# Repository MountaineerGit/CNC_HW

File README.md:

STM32 breakoutboard for custom CNC machine

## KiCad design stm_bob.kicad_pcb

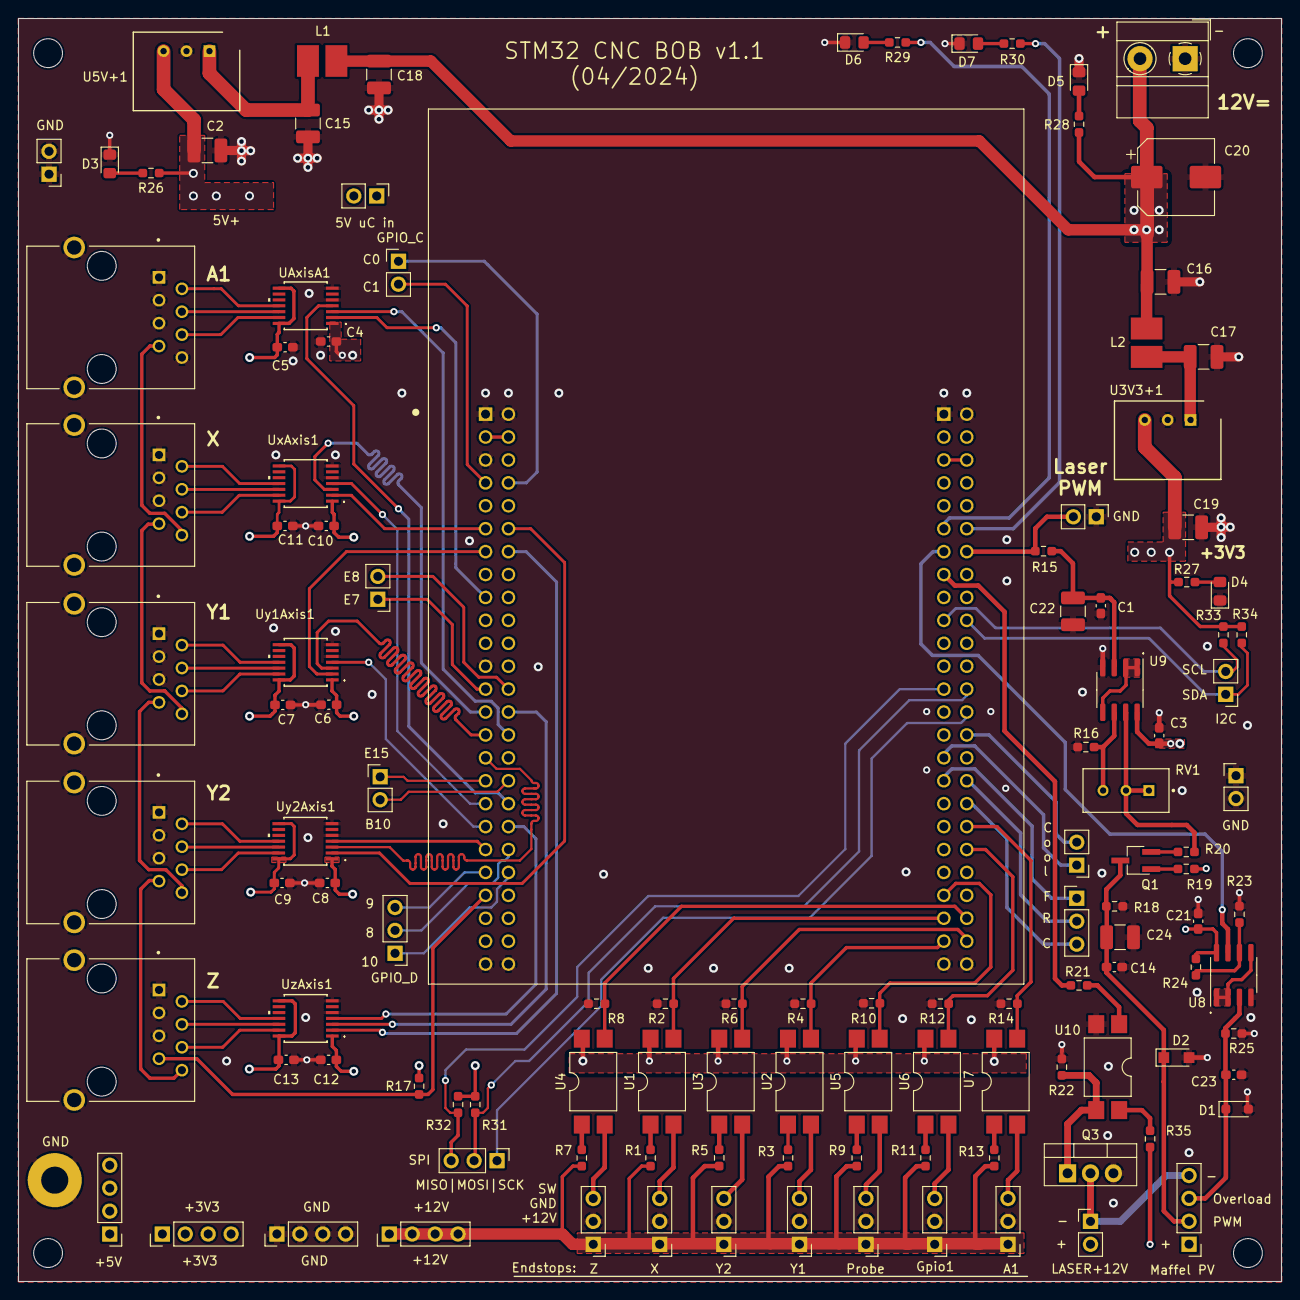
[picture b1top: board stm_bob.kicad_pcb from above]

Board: 4 copper layers, 140.0 x 140.0 mm, 125 parts (0 on the bottom side), 107 nets.

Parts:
C1, C21: 100n; C_0603_1608Metric_Pad1.08x0.95mm_HandSolder
C2, C15, C16, C17, C18, C19: 10uF 100V MCC; L_1210_3225Metric_Pad1.42x2.65mm_HandSolder
C3, C4, C5, C6, C7, C8, C9, C10, C11, C12, C13, C14: C; C_0603_1608Metric_Pad1.08x0.95mm_HandSolder
C20: C_Polarized; CP_Elec_8x10
C22, C24: 10uF; L_1210_3225Metric_Pad1.42x2.65mm_HandSolder
C23: 10pf; C_0603_1608Metric_Pad1.08x0.95mm_HandSolder
D1: 10V; D_SOD-323_HandSoldering
D2: D_Zener; Nexperia_CFP3_SOD-123W
D3, D4, D5, D6, D7: LED; D_0805_2012Metric_Pad1.15x1.40mm_HandSolder
H1, H2, H3, H4: MountingHole; MountingHole_3.2mm_M3
H5: MountingHole_Pad; MountingHole_3mm_Pad
J1: Conn_01x02; TerminalBlock_MetzConnect_Type011_RT05502HBWC_1x02_P5.00mm_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
J2, J3, J5, J6: Conn_01x04_Pin; PinHeader_1x04_P2.54mm_Vertical
J4, J7: Conn_01x02_Pin; PinHeader_1x02_P2.54mm_Vertical
J9_GPIO1, J9_GPIO2, J9_GPIO3, J9_GPIO4, J10_GPIO1: Conn_01x02; PinHeader_1x02_P2.54mm_Vertical
J11_GPIO1, J11_SPI1, J11_SPI2: Conn_01x03; PinHeader_1x03_P2.54mm_Vertical
JAxisA1: A-2004-2-4-LPS-N-R; ASSMANN_A-2004-2-4-LPS-N-R
JGpio1: Conn_01x03_Pin; PinHeader_1x03_P2.54mm_Vertical
JI2C1: Conn_01x02; PinHeader_1x02_P2.54mm_Vertical
JLaser12V1: Conn_01x02_Pin; PinHeader_1x02_P2.54mm_Vertical
JLaserPWM1: Conn_01x02_Pin; PinHeader_1x02_P2.54mm_Vertical
JProbe1: Conn_01x03_Pin; PinHeader_1x03_P2.54mm_Vertical
JPvMaffel1: Conn_01x04_Pin; PinHeader_1x04_P2.54mm_Vertical
JlimA1: Conn_01x03_Pin; PinHeader_1x03_P2.54mm_Vertical
JlimX1: Conn_01x03_Pin; PinHeader_1x03_P2.54mm_Vertical
JlimY1, JlimY2: Conn_01x03_Pin; PinHeader_1x03_P2.54mm_Vertical
JlimZ1: Conn_01x03_Pin; PinHeader_1x03_P2.54mm_Vertical
JxAxis1: A-2004-2-4-LPS-N-R; ASSMANN_A-2004-2-4-LPS-N-R
Jy1Axis1, Jy2Axis1: A-2004-2-4-LPS-N-R; ASSMANN_A-2004-2-4-LPS-N-R
JzAxis1: A-2004-2-4-LPS-N-R; ASSMANN_A-2004-2-4-LPS-N-R
L1, L2: L; IND_S-126-R_RCP
Q1: NPN; TSOT-23_HandSoldering
Q3: IRF3205; TO-220-3_Vertical
R1, R3, R5, R7, R9, R11, R13, R15, R28, R35: 1k; R_0603_1608Metric_Pad0.98x0.95mm_HandSolder
R2, R4, R6, R8, R10, R12, R14, R17, R23, R31, R32, R33, R34: 3k3; R_0603_1608Metric_Pad0.98x0.95mm_HandSolder
R16: 47k; R_0603_1608Metric_Pad0.98x0.95mm_HandSolder
R18, R19, R20: R; R_0603_1608Metric_Pad0.98x0.95mm_HandSolder
R21, R27: 430; R_0603_1608Metric_Pad0.98x0.95mm_HandSolder
R22: 2k; R_0603_1608Metric_Pad0.98x0.95mm_HandSolder
R24: 2k2; R_0603_1608Metric_Pad0.98x0.95mm_HandSolder
R25: 100k; R_0603_1608Metric_Pad0.98x0.95mm_HandSolder
R26: 470; R_0603_1608Metric_Pad0.98x0.95mm_HandSolder
R29, R30: 510; R_0603_1608Metric_Pad0.98x0.95mm_HandSolder
RV1: 100k; TRIM_3296W-1-332LF
TB1: STM32F4DISCOVERY; MODULE_STM32F4DISCOVERY
U1, U2, U3, U4, U5, U6, U7, U10: LTV-817S; SMDIP-4_W9.53mm
U3V3+1: R-78E3.3-1.0; SIP3_11.6x8.5mm
U5V+1: R-78E5.0-1.0; SIP3_11.6x8.5mm
U8, U9: LM358; SOIC-8_3.9x4.9mm_P1.27mm
UAxisA1: PTXU0104QPWRQ1; TSSOP_QPWRQ1_TEX
UxAxis1: PTXU0104QPWRQ1; TSSOP_QPWRQ1_TEX
Uy1Axis1, Uy2Axis1: PTXU0104QPWRQ1; TSSOP_QPWRQ1_TEX
UzAxis1: PTXU0104QPWRQ1; TSSOP_QPWRQ1_TEX

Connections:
+3V3: C4.1, C6.1, C8.1, C10.1, C12.1, C19.1, C21.1, J3.1, J3.2, J3.3, J3.4, R17.1, R24.2, R27.1, R31.1, R32.1, R33.1, R34.1, TB1.P2_5 (3V), TB1.P2_6 (3V), U1.4, U2.4, U3.4, U3V3+1.3 (+VOUT), U4.4, U5.4, U6.4, U7.4, U8.8 (V+), UAxisA1.1 (VCCA), UxAxis1.1 (VCCA), Uy1Axis1.1 (VCCA), Uy2Axis1.1 (VCCA), UzAxis1.1 (VCCA)
+5V: C2.1, C5.1, C7.1, C9.1, C11.1, C13.1, J2.1, J2.2, J2.3, J2.4, J9_GPIO2.2, R26.1, U5V+1.3 (+VOUT), UAxisA1.8 (OE), UAxisA1.14 (VCCB), UxAxis1.8 (OE), UxAxis1.14 (VCCB), Uy1Axis1.8 (OE), Uy1Axis1.14 (VCCB), Uy2Axis1.8 (OE), Uy2Axis1.14 (VCCB), UzAxis1.8 (OE), UzAxis1.14 (VCCB)
+12V: C3.1, C16.1, C18.1, C20.1, J1.2, J5.1, J5.2, J5.3, J5.4, JGpio1.1, JLaser12V1.2, JProbe1.1, JPvMaffel1.1, JlimA1.1, JlimX1.1, JlimY1.1, JlimY2.1, JlimZ1.1, L1.1, L2.1, R1.1, R3.1, R5.1, R7.1, R9.1, R11.1, R13.1, R19.2, R28.1, R35.1, U9.8 (V+)
/PWM/Vref: R23.2, R24.1, U8.6 (-)
/dirA_: JAxisA1.6, UAxisA1.13 (B1Y)
/dirX_: JxAxis1.6, UxAxis1.13 (B1Y)
/dirY1_: Jy1Axis1.6, Uy1Axis1.13 (B1Y)
/dirY2_: Jy2Axis1.6, Uy2Axis1.13 (B1Y)
/dirZ_: JzAxis1.6, UzAxis1.13 (B1Y)
/enableA_: JAxisA1.2, UAxisA1.11 (B3Y)
/enableX_: JxAxis1.2, UxAxis1.11 (B3Y)
/enableY1_: Jy1Axis1.2, Uy1Axis1.11 (B3Y)
/enableY2_: Jy2Axis1.2, Uy2Axis1.11 (B3Y)
/enableZ_: JzAxis1.2, UzAxis1.11 (B3Y)
/errorA_+: JAxisA1.7, JxAxis1.8
/errorX_+: JxAxis1.7, Jy1Axis1.8
/errorY1_+: Jy1Axis1.7, Jy2Axis1.8
/errorY2_+: Jy2Axis1.7, JzAxis1.8
/stepA_: JAxisA1.4, UAxisA1.12 (B2Y)
/stepX_: JxAxis1.4, UxAxis1.12 (B2Y)
/stepY1_: Jy1Axis1.4, Uy1Axis1.12 (B2Y)
/stepY2_: Jy2Axis1.4, Uy2Axis1.12 (B2Y)
/stepZ_: JzAxis1.4, UzAxis1.12 (B2Y)
CycleStart: J11_SPI2.3, TB1.P2_36 (PD0)
FeedHold: J11_SPI2.1, TB1.P2_33 (PD1)
GND: C1.2, C2.2, C3.2, C4.2, C5.2, C6.2, C7.2, C8.2, C9.2, C10.2, C11.2, C12.2, C13.2, C14.2, C15.2, C16.2, C17.2, C18.2, C19.2, C20.2, C21.2, C22.2, C23.2, C24.2, D1.2 (A), D2.2 (A), D3.1 (K), D4.1 (K), D5.1 (K), D6.1 (K), D7.1 (K), H5.1, J1.1, J4.1, J4.2, J6.1, J6.2, J6.3, J6.4, J7.1, J7.2, JAxisA1.1, JAxisA1.3, JAxisA1.5, JAxisA1.8, JAxisA1.S1 (SHIELD), JAxisA1.S2 (SHIELD), JGpio1.2, JLaserPWM1.1, JProbe1.2, JlimA1.2, JlimX1.2, JlimY1.2, JlimY2.2, JlimZ1.2, JxAxis1.1, JxAxis1.3, JxAxis1.5, JxAxis1.S1 (SHIELD), JxAxis1.S2 (SHIELD), Jy1Axis1.1, Jy1Axis1.3, Jy1Axis1.5, Jy1Axis1.S1 (SHIELD), Jy1Axis1.S2 (SHIELD), Jy2Axis1.1, Jy2Axis1.3, Jy2Axis1.5, Jy2Axis1.S1 (SHIELD), Jy2Axis1.S2 (SHIELD), JzAxis1.1, JzAxis1.3, JzAxis1.5, JzAxis1.S1 (SHIELD), JzAxis1.S2 (SHIELD), Q3.3 (S), R2.2, R4.2, R6.2, R8.2, R10.2, R12.2, R14.2, R16.1, R18.1, R22.2, R23.1, R25.1, TB1.P1_1 (GND), TB1.P1_2 (GND), TB1.P1_5 (GND), TB1.P1_23 (GND), TB1.P1_49 (GND), TB1.P1_50 (GND), TB1.P2_1 (GND), TB1.P2_2 (GND), TB1.P2_49 (GND), TB1.P2_50 (GND), U3V3+1.2 (GND), U5V+1.2 (GND), U8.4 (V-), U9.4 (V-), U10.2, UAxisA1.5 (A4), UAxisA1.7 (GND), UxAxis1.5 (A4), UxAxis1.7 (GND), Uy1Axis1.5 (A4), Uy1Axis1.7 (GND), Uy2Axis1.5 (A4), Uy2Axis1.7 (GND), UzAxis1.5 (A4), UzAxis1.7 (GND)
GPIO1: R12.1, TB1.P2_40 (PA15), U6.3
GPIO_B10: J9_GPIO1.2, TB1.P1_34 (PB10)
GPIO_E7: J10_GPIO1.1, TB1.P1_25 (PE7)
GPIO_E8: J10_GPIO1.2, TB1.P1_26 (PE8)
GPIO_E15: J9_GPIO1.1, TB1.P1_33 (PE15)
GPIO_PC0: J9_GPIO3.1, TB1.P1_8 (PC0)
GPIO_PC1: J9_GPIO3.2, TB1.P1_7 (PC1)
GPIO_PD08: J11_GPIO1.2, TB1.P1_40 (PD8)
GPIO_PD09: J11_GPIO1.3, TB1.P1_41 (PD9)
GPIO_PD10: J11_GPIO1.1, TB1.P1_42 (PD10)
I2C_SCL: JI2C1.2, R33.2, TB1.P2_19 (PB8)
I2C_SDA: JI2C1.1, R34.2, TB1.P2_20 (PB9)
LED1: R29.1, TB1.P2_11 (PE6)
LED2: R30.1, TB1.P2_12 (PC13)
unnamed: D3.2 (A), R26.2
unnamed: D4.2 (A), R27.2
unnamed: D5.2 (A), R28.2
unnamed: D6.2 (A), R29.2
unnamed: D7.2 (A), R30.2
unnamed: J9_GPIO2.1, TB1.P2_3 (5V), TB1.P2_4 (5V)
unnamed: JGpio1.3, U6.2
unnamed: JLaser12V1.1, JPvMaffel1.4, Q3.2 (D)
unnamed: JProbe1.3, U5.2
unnamed: JlimA1.3, U7.2
unnamed: JlimX1.3, U1.2
unnamed: JlimY1.3, U2.2
unnamed: JlimY2.3, U3.2
unnamed: JlimZ1.3, U4.2
unnamed: Q1.2 (B), R20.1
unnamed: Q1.1 (C), R19.1
unnamed: Q3.1 (G), R22.1, U10.3
unnamed: R1.2, U1.1
unnamed: R3.2, U2.1
unnamed: R5.2, U3.1
unnamed: R7.2, U4.1
unnamed: R9.2, U5.1
unnamed: R11.2, U6.1
unnamed: R13.2, U7.1
unnamed: R20.2, RV1.1, RV1.2, U9.7
unnamed: R21.2, U10.1
unnamed: R35.2, U10.4
unnamed: C17.1, L2.2, U3V3+1.1 (+VIN)
unnamed: C15.1, L1.2, U5V+1.1 (+VIN)
unnamed: U8.1, U8.2 (-), U8.5 (+)
unnamed: C1.1, C22.1, R15.2, U9.3 (+)
unnamed: U9.1, U9.2 (-), U9.5 (+)
unnamed: R16.2, RV1.3, U9.6 (-)
Probe: R10.1, TB1.P2_43 (PA8), U5.3
Reset: J11_SPI2.2, TB1.P2_34 (PD2)
SPI_MISO: J11_SPI1.3, R32.2, TB1.P2_25 (PB4)
SPI_MOSI: J11_SPI1.2, R31.2, TB1.P2_26 (PB5)
SPI_SCK: J11_SPI1.1, TB1.P2_28 (PB3)
SpindleEnable: R21.1, TB1.P2_15 (PE2)
SpindleOverload: TB1.P2_13 (PE4), U8.7
SpindlePWM: JLaserPWM1.2, R15.1, TB1.P2_14 (PE5)
Uo_overload: C23.1, D1.1 (K), JPvMaffel1.3, R25.2, U8.3 (+)
Upv_maffel: C14.1, C24.1, D2.1 (K), JPvMaffel1.2, Q1.3 (E), R18.2
VDD: TB1.P1_3 (VDD), TB1.P1_4 (VDD), TB1.P2_22 (VDD)
coolant_flood: J9_GPIO4.1, TB1.P2_31 (PD3)
coolant_mist: J9_GPIO4.2, TB1.P2_30 (PD6)
dirA: TB1.P1_17 (PA7), UAxisA1.2 (A1)
dirX: TB1.P1_11 (PA1), UxAxis1.2 (A1)
dirY1: TB1.P1_13 (PA3), Uy1Axis1.2 (A1)
dirY2: TB1.P1_12 (PA0-WKUP), Uy2Axis1.2 (A1)
dirZ: TB1.P1_14 (PA2), UzAxis1.2 (A1)
enableA: TB1.P1_36 (PB12), UAxisA1.4 (A3)
enableX: TB1.P1_35 (PB11), UxAxis1.4 (A3)
enableY1: TB1.P1_37 (PB13), Uy1Axis1.4 (A3)
enableY2: TB1.P1_39 (PB15), Uy2Axis1.4 (A3)
enableZ: TB1.P1_38 (PB14), UzAxis1.4 (A3)
error_stepper: JzAxis1.7, R17.2, TB1.P1_43 (PD11)
limitA: R14.1, TB1.P2_38 (PC11), U7.3
limitX: R2.1, TB1.P2_45 (PC8), U1.3
limitY1: R4.1, TB1.P2_47 (PC6), U2.3
limitY2: R6.1, TB1.P2_48 (PC7), U3.3
limitZ: R8.1, TB1.P2_46 (PC9), U4.3
stepA: TB1.P1_30 (PE12), UAxisA1.3 (A2)
stepX: TB1.P1_27 (PE9), UxAxis1.3 (A2)
stepY1: TB1.P1_29 (PE11), Uy1Axis1.3 (A2)
stepY2: TB1.P1_31 (PE13), Uy2Axis1.3 (A2)
stepZ: TB1.P1_28 (PE10), UzAxis1.3 (A2)

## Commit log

2023-12-22 Initial commit PCB files
2023-12-31 Version 1.1 - reworked all smd's to 0603
2024-03-10 Updating 12V on/off with FET now; Laser connectors added
2024-03-12 Make GND vias larger, some cleanups
2024-03-31 Adding Coolant and Mist; some GPIOs added
2024-04-01 Updating for version 1.1
2024-04-01 save only
2024-04-01 submitted to JLCPCB
2024-10-16 Mainly value updates
2024-10-16 make mounting holes M3 friendly (3.2mm)
2024-10-16 Adding schematic.pdf and pcb.pdf
2024-10-16 properly connected moved 12V connector
